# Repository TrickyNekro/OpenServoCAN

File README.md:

# OpenServoCAN
by El. Provatos

<b>!!! Currently two versions of the Hardware exist, development is going to continue on version 2 !!!</b><br>
<b>!!! Note: There is a design problem ( mechanical fitting ) with the power board, wait for update !!!</b>

An alternative to the boring control boards inside standard size hobby servos!

As it is, the project is far from completion! I have the first boards already, but I do not
have the materials to populate them. I will most probably start a gofundme campaign for these
first stages of the project. So bear with me, this will be an on-going process!

It was a very long time I wanted to make a project like this
Most, for the more expensive ones, hobby servos offer no feed back.
You send them a signal and hope they will reach the targeted position.
This might be good enough for uses in the RC world, but not good enough 
at all for those building robots or anything of a kind that needs feedback.

And thus this project was born! Although I am aware that another OpenServo Project
exists, I wanted to put my own touch into the matter and I tried to do quite a few 
things better, at least compared to the first version (I have not reviewed the second).

- Hardware V1 Capabilities

1) Added CAN-Bus! Yes, that´s a good thing! It might complicate some things especially for beginners
but that´s on what most "unobtainium" servos work in the market. I have not yet decided the 
communications protocol, but I am leaning towards CANopen, suggestions are open!

2) Can support either a potentiometer or an encoder (quadrature or not) for positional control

3) Can operate from 5V - 15V safe zone, but most probably will not have a problem with a 4S LiPo.
Current limiting will be done by software so, if you want to break the DC motor inside or not is
totally up to you!

4) Beefed up MOSFETs with individual MOSFET drivers, just to be able to push that switching 
frequency to the right spot without worrying too much!

- Hardware V2 Capabilities ( added on top of the previous! )

1) Modular! Yes, Modular! There is a Power Board, a CPU / MCU board and a Sensor / Encoder Board.
All are connected on the same bus, through some nice 0,5mm pitch - 30 pin Amphenol connectors. 
That also means of course that everything can change, and the version in connected to the function
specific board and not the whole system. Bored of the microcontroller? Change the MCU board, need
higher voltage? Change the power board? Need more capabilities? If physically allowed, add more
boards! Etc. etc. etc.. 

2) This version uses a magnetic encoder from AMS! Have not tested it yet, but given that it works
well without much interference from the motor, it should be able to give both precision, speed and
universality to the adaptation of the design. And do not forget... bored of the encoder board? Need
something more simple? Design and change it with a potentiometer board! Easy Peasy!!! 

3) One of the main limitation of the previous version was the input voltage. 15V max? How boring! 
This version was aimed to work with 24V and pushing it to 30V should be no problem! Unfortunately
the 100% duty cycle capability is gone as well, but the more efficient all N-Channel MOSFET bridge
should be able to make up the difference! Even if it does not, this was the one big step in being
able to bridge the design to a higher operating voltage, given the much constrained space.

4) There is a digital power meter from Texas Instruments on-board, should offload the processor 
quite a bit! And has also some quite interesting interrupt capabilites that should come in handy.

5) MCU board now has, EEPROM, battery (or better Super-Cap) backed RTC, a temperature sensor and
an RGB LED! How can one live without RGB these days. In all seriousness though, the RTC and EEPROM
should be a good compination for logging data / events and or even be used to wake the device up,
or even be able to develop small scripts for the device to run autonomously. But that´s only a dream
for now, still capability is there!

6) Reverse polarity protection is still here! But I also added some small extras! Some "TVS - like"
suppressors here, some more distributed capacitance there. It should be less noisy and more stable.
Only time will tell as more and more code and testing is being done!

<b> Important 2/11/2020 Update! </b>
I have officially ended the fundraiser for this Project. True to my promise I would like to thank:
Juri Ludwig, Anonymous (from eevblog ;-) ), Vagelis Logaras and Andreas Efthymiadis for their contributions.
Their money have funded a couple mouser orders, the PCBs and some test servos. Which for me is more than
enough that anyone would do for an open project with an open completion date! I can only promise that I
will continue to deliver as much as real life allows me. Thank you! Let your names be immortalized here!

# Donations!

<b>No need :) </b>

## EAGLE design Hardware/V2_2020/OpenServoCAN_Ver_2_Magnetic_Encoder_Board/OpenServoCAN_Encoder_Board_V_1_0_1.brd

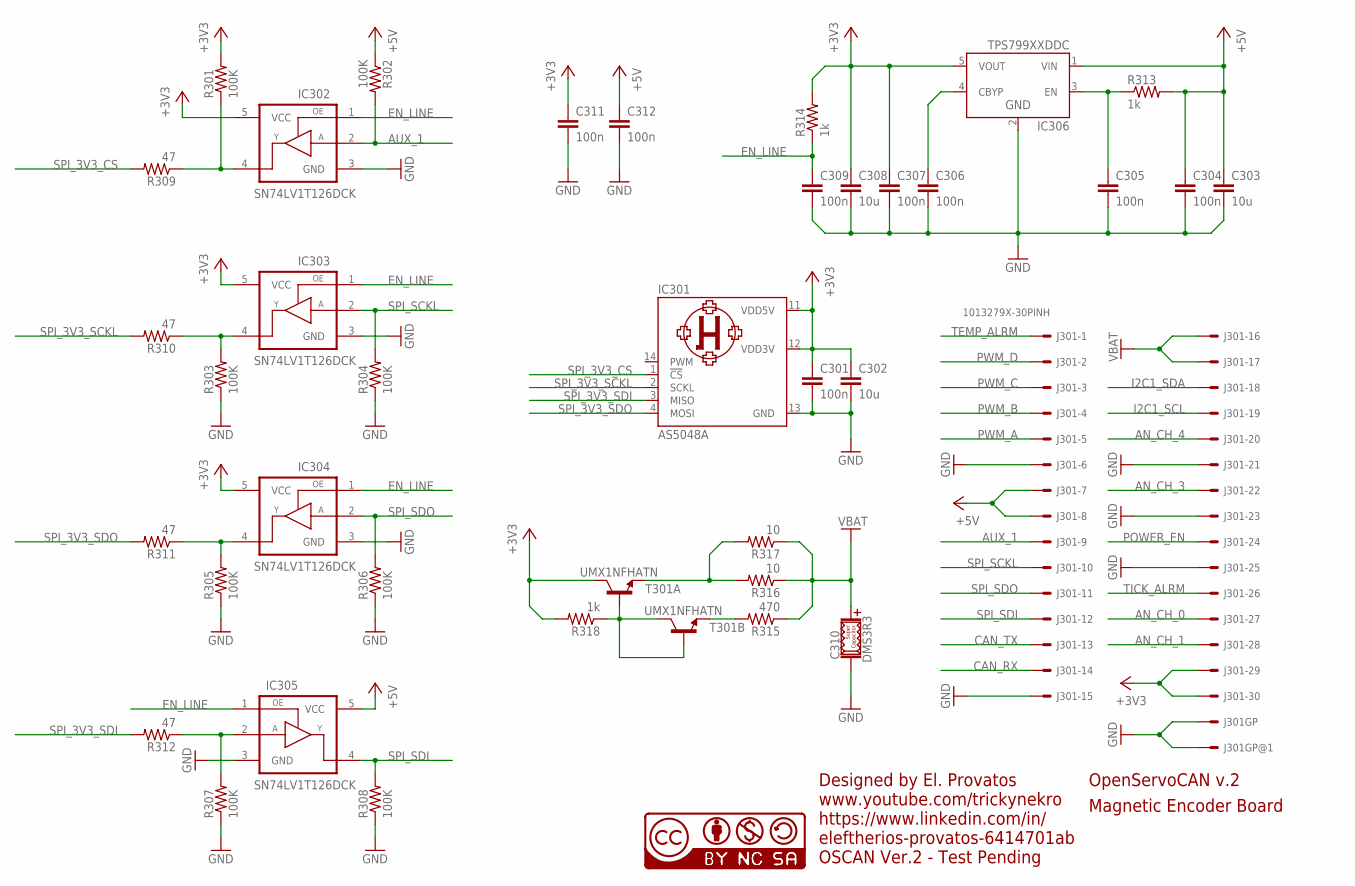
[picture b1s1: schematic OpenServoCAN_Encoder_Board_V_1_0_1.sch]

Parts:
C301, C304, C305, C306, C307, C309, C311, C312: 100n; 0402_C
C302, C303, C308: 10u; 0402_C
C310: DMS3R3; DMS_3R3_S_CAP
IC301: AS5048A; TSSOP-14
IC302, IC303, IC304, IC305: SN74LV1T126DCK; SC-70-5
IC306: TPS799XXDDC; SOT-23-5
J301: 1013279X-30PINH; 10132797-30
R301, R302, R303, R304, R305, R306, R307, R308: 100K; 0402_R
R309, R310, R311, R312: 47; 0402_R
R313, R314, R318: 1k; 0402_R
R315: 470; 0402_R
R316, R317: 10; 0402_R
T301: UMX1NFHATN; SC-70-6
U$1: CC-NC-BCNIX; CC-NC-B_NIX

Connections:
+3V3: C301.1, C302.1, C307.1, C308.1, C311.1, IC301.11 (VDD5V), IC301.12 (VDD3V), IC302.5 (VCC), IC303.5 (VCC), IC304.5 (VCC), IC306.5 (VOUT), J301.29, J301.30, R301.2, R314.2, R318.2, T301.6 (C)
+5V: C303.1, C304.1, C312.1, IC305.5 (VCC), IC306.1 (VIN), J301.7, J301.8, R302.1, R313.2
AN_CH_0: J301.27
AN_CH_1: J301.28
AN_CH_3: J301.22
AN_CH_4: J301.20
AUX_1: IC302.2 (A), J301.9, R302.2
CAN_RX: J301.14
CAN_TX: J301.13
EN_LINE: C309.1, IC302.1 (OE), IC303.1 (OE), IC304.1 (OE), IC305.1 (OE), R314.1
GND: C301.2, C302.2, C303.2, C304.2, C305.2, C306.2, C307.2, C308.2, C309.2, C310.NEG- (NEG), C311.2, C312.2, IC301.13 (GND), IC302.3 (GND), IC303.3 (GND), IC304.3 (GND), IC305.3 (GND), IC306.2 (GND), J301.6, J301.15, J301.21, J301.23, J301.25, J301.EP@2, J301.EP@↑1, R303.1, R304.1, R305.1, R306.1, R307.1, R308.1
I2C1_SCL: J301.19
I2C1_SDA: J301.18
unnamed: R318.1, T301.2 (B), T301.3 (C), T301.5 (B)
unnamed: C306.1, IC306.4 (CBYP)
unnamed: R316.2, R317.2, T301.1 (E)
unnamed: IC305.2 (A), R307.2, R312.1
unnamed: C305.1, IC306.3 (EN), R313.1
unnamed: IC304.4 (Y), R305.2, R311.1
unnamed: R315.2, T301.4 (E)
unnamed: IC303.4 (Y), R303.2, R310.1
unnamed: IC302.4 (Y), R301.1, R309.1
POWER_EN: J301.24
PWM_A: J301.5
PWM_B: J301.4
PWM_C: J301.3
PWM_D: J301.2
SPI_3V3_CS: IC301.1 (!CS), R309.2
SPI_3V3_SCKL: IC301.2 (SCKL), R310.2
SPI_3V3_SDI: IC301.3 (MISO), R312.2
SPI_3V3_SDO: IC301.4 (MOSI), R311.2
SPI_SCKL: IC303.2 (A), J301.10, R304.2
SPI_SDI: IC305.4 (Y), J301.12, R308.2
SPI_SDO: IC304.2 (A), J301.11, R306.2
TEMP_ALRM: J301.1
TICK_ALRM: J301.26
VBAT: C310.POS+ (POS), J301.16, J301.17, R315.1, R316.1, R317.1

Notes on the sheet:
OpenServoCAN v.2
Magnetic Encoder Board
Designed by El. Provatos
www.youtube.com/trickynekro
https://www.linkedin.com/in/ eleftherios-provatos-6414701ab
OSCAN Ver.2 - Test Pending

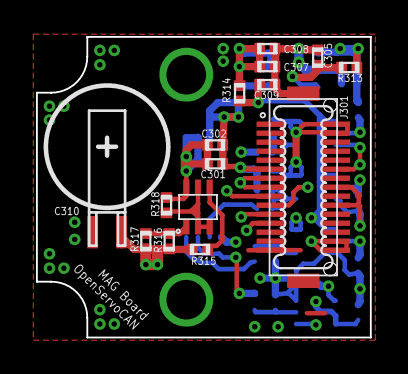
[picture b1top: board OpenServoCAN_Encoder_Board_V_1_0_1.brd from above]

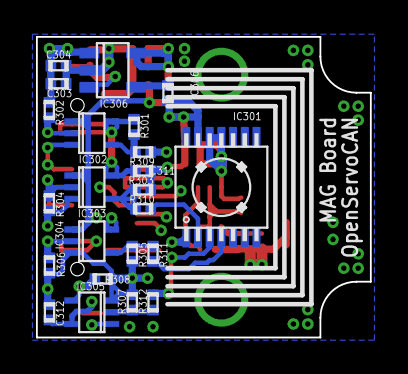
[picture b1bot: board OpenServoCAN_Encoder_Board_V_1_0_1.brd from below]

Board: 4 copper layers, 18.6 x 16.7 mm, 39 parts (23 on the bottom side), 22 nets.

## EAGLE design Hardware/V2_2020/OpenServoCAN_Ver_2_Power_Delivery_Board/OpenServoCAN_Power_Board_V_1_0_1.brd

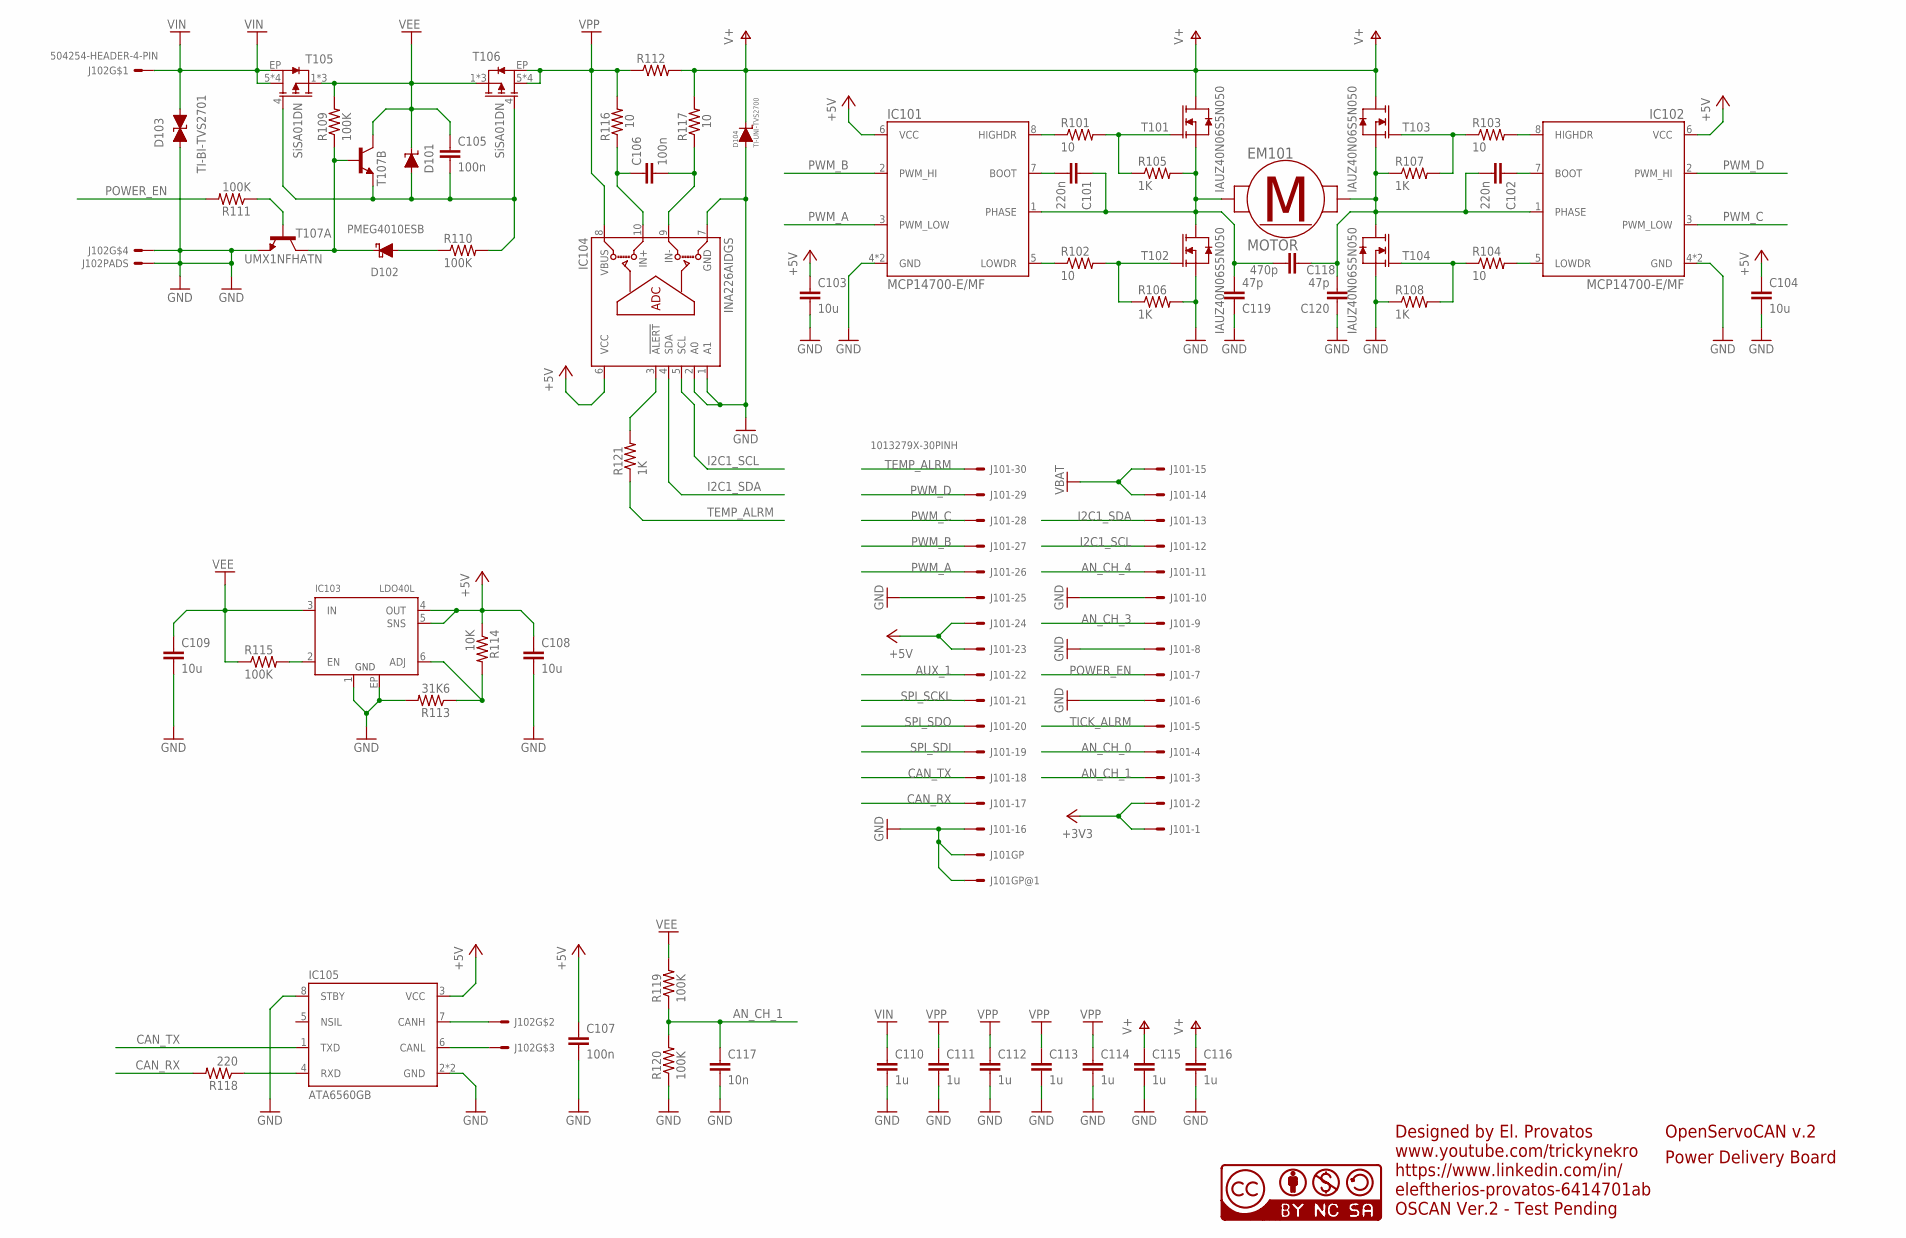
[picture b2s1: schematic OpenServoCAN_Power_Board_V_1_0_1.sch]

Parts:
C101, C102: 220n; 0603_C
C103, C104, C108, C109: 10u; 0402_C
C105, C106, C107: 100n; 0402_C
C110, C111, C112, C113, C114, C115, C116: 1u; 0603_C
C117: 10n; 0402_C
C118: 470p; 1206_C
C119, C120: 47p; 1206_C
D101: DDZ12CSF; SOD-323
D102: PMEG4010ESB; DSN1006-2
D103: TI-BI-TVS2701; VSON-8-DRB0008A
D104: TI-UNI-TVS2700; WSON-6
EM101: MOTOR; RF-020TH-10210
IC101, IC102: MCP14700-E/MF; DFN_8_3X3X09_MF_MICROCHIP
IC103: LDO40L; DFN6-3X3
IC104: INA226AIDGS; VSSOP-10
IC105: ATA6560GB; VDFN-8-EP
J101: 1013279X-30PINH; 10132797-30
J102: 504254-HEADER-4-PIN; 504254
R101, R102, R103, R104, R116, R117: 10; 0402_R
R105, R106, R107, R108, R121: 1K; 0402_R
R109, R110, R111, R115, R119, R120: 100K; 0402_R
R112: TLR2HW-R-US-SENSE; TLR2HW
R113: 31K6; 0402_R
R114: 10K; 0402_R
R118: 220; 0402_R
T101, T102, T103, T104: IAUZ40N06S5N050; PG-TSDSON-8-33-INF
T105, T106: SiSA01DN; POWERPAK-1212-8-SINGLE
T107: UMX1NFHATN; SC-70-6
U$1: CC-NC-BCNIX; CC-NC-B_NIX

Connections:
+3V3: J101.1, J101.2
+5V: C103.1, C104.1, C107.1, C108.1, IC101.6 (VCC), IC102.6 (VCC), IC103.4 (OUT), IC103.5 (SNS), IC104.6 (VCC), IC105.3 (VCC), J101.23, J101.24, R114.1
AN_CH_0: J101.4
AN_CH_1: C117.1, J101.3, R119.1, R120.2
AN_CH_3: J101.9
AN_CH_4: J101.11
AUX_1: J101.22
CAN_RX: J101.17, R118.2
CAN_TX: IC105.1 (TXD), J101.18
GND: C103.2, C104.2, C107.2, C108.2, C109.2, C110.2, C111.2, C112.2, C113.2, C114.2, C115.2, C116.2, C117.2, C119.1, C120.1, D103.5 (A), D103.6 (A), D103.7 (A), D103.8 (A), D104.1 (A), D104.2 (A), D104.3 (A), D104.EP (A), IC101.4 (GND), IC101.EP (GND), IC102.4 (GND), IC102.EP (GND), IC103.1 (GND), IC103.EP (GND), IC104.1 (A1), IC104.2 (A0), IC104.7 (GND), IC105.2 (GND), IC105.8 (STBY), IC105.EP (GND), J101.6, J101.8, J101.10, J101.16, J101.25, J101.EP@2, J101.EP@↑1, J102.4, J102.EP@1, J102.EP@2, J102.EP@3, J102.EP@4, R106.2, R108.1, R113.2, R120.1, T102.S, T104.S, T107.1 (E)
I2C1_SCL: IC104.5 (SCL), J101.12
I2C1_SDA: IC104.4 (SDA), J101.13
unnamed: C101.1, C118.2, C119.2, EM101.1B (1), EM101.1T (1), IC101.1 (PHASE), R105.2, T101.S, T102.D
unnamed: C102.2, C118.1, C120.2, EM101.2B (2), EM101.2T (2), IC102.1 (PHASE), R107.1, T103.S, T104.D
unnamed: R103.1, R107.2, T103.G
unnamed: IC101.8 (HIGHDR), R101.1
unnamed: R101.2, R105.1, T101.G
unnamed: IC102.8 (HIGHDR), R103.2
unnamed: IC104.3 (!ALERT), R121.2
unnamed: R102.2, R106.1, T102.G
unnamed: IC101.5 (LOWDR), R102.1
unnamed: R104.1, R108.2, T104.G
unnamed: IC102.5 (LOWDR), R104.2
unnamed: C102.1, IC102.7 (BOOT)
unnamed: IC103.6 (ADJ), R113.1, R114.2
unnamed: C101.2, IC101.7 (BOOT)
unnamed: IC103.2 (EN), R115.2
unnamed: C106.1, IC104.10 (IN+), R116.1
unnamed: C106.2, IC104.9 (IN-), R117.1
unnamed: IC105.7 (CANH), J102.2
unnamed: IC105.6 (CANL), J102.3
unnamed: D102.K, R109.1, T107.5 (B), T107.6 (C)
unnamed: D102.A, R110.1
unnamed: C105.2, D101.A, R110.2, T105.4 (G), T106.4 (G), T107.4 (E)
unnamed: R111.1, T107.2 (B)
unnamed: IC105.4 (RXD), R118.1
POWER_EN: J101.7, R111.2
PWM_A: IC101.3 (PWM_LOW), J101.26
PWM_B: IC101.2 (PWM_HI), J101.27
PWM_C: IC102.3 (PWM_LOW), J101.28
PWM_D: IC102.2 (PWM_HI), J101.29
SPI_SCKL: J101.21
SPI_SDI: J101.19
SPI_SDO: J101.20
TEMP_ALRM: J101.30, R121.1
TICK_ALRM: J101.5
V+: C115.1, C116.1, D104.4 (K), D104.5 (K), D104.6 (K), R112.2, R117.2, T101.D, T103.D
VBAT: J101.14, J101.15
VEE: C105.1, C109.1, D101.K, IC103.3 (IN), R109.2, R115.1, R119.2, T105.1 (S), T105.2 (S), T105.3 (S), T106.1 (S), T106.2 (S), T106.3 (S), T107.3 (C)
VIN: C110.1, D103.1 (K), D103.2 (K), D103.3 (K), D103.4 (K), J102.1, T105.5 (D), T105.6 (D), T105.7 (D), T105.8 (D), T105.EP (D)
VPP: C111.1, C112.1, C113.1, C114.1, IC104.8 (VBUS), R112.1, R116.2, T106.5 (D), T106.6 (D), T106.7 (D), T106.8 (D), T106.EP (D)

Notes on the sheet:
Designed by El. Provatos
www.youtube.com/trickynekro
https://www.linkedin.com/in/ eleftherios-provatos-6414701ab
OSCAN Ver.2 - Test Pending
OpenServoCAN v.2
Power Delivery Board

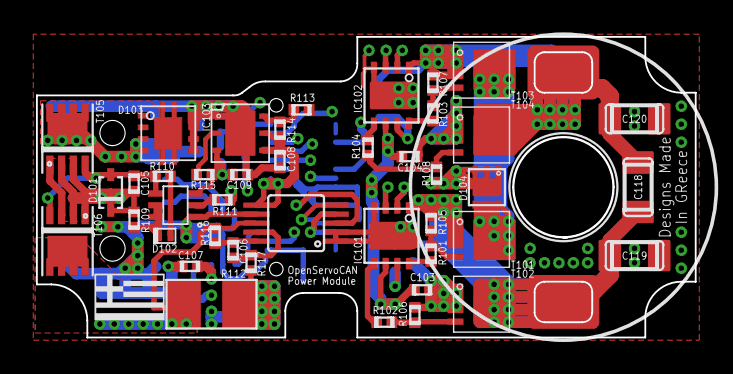
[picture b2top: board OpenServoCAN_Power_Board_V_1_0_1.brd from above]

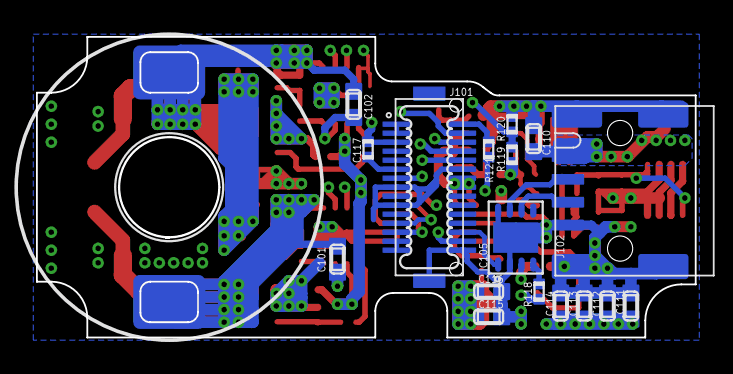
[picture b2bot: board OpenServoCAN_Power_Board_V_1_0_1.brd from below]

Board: 4 copper layers, 36.6 x 16.7 mm, 61 parts (18 on the bottom side), 43 nets.

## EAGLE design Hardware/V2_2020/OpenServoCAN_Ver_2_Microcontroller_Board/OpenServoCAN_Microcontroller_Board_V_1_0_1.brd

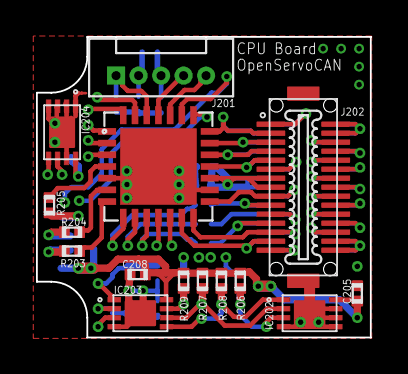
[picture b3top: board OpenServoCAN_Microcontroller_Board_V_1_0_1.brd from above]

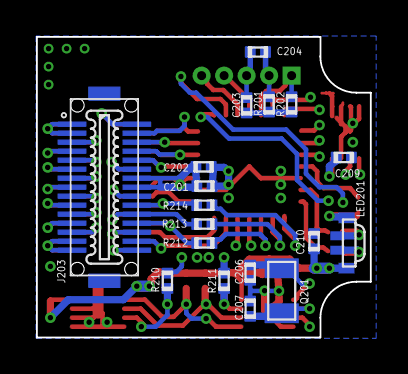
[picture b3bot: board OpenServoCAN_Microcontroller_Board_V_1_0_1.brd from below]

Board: 4 copper layers, 18.6 x 16.7 mm, 35 parts (18 on the bottom side), 40 nets.

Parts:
C201, C203, C204, C205, C208, C209, C210: 100n; 0402_C
C202: 2u2; 0402_C
C206, C207: 22p; 0402_C
IC201: QFN-28
IC202: MCP9808T-E/MC; DFN_2X3_MICROCHIP
IC203: MCP7940N; DFN_2X3_MICROCHIP
IC204: 24XX64MC; DFN_2X3_MICROCHIP
J201: PICOBLADE-5
J202, J203: 1013279X-30PINR; 10132798-30
LED201: 1206_RGB_LED
LOGO1: TRN_LOGO_INV; TRN_LOGO_2020_INV
Q201: LFXTAL009678
R201, R206, R207, R208, R209: 4k7; 0402_R
R202, R210, R211: 470; 0402_R
R203, R204, R205: 220; 0402_R
R212, R213, R214: 47; 0402_R
U$1: CC-NC-BCNIX; CC-NC-B_NIX

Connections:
+3V3: J202.29, J202.30, J203.1, J203.2
+5V: C201.1, C202.1, C204.1, C205.1, C208.1, C209.1, C210.1, IC201.17, IC202.8, IC203.8, IC204.8, J201.2, J202.7, J202.8, J203.23, J203.24, LED201.3, R201.2, R206.2, R207.2, R208.2, R209.2
AN_CH_0: IC201.27, J202.27, J203.4
AN_CH_1: IC201.28, J202.28, J203.3
AN_CH_3: IC201.2, J202.22, J203.9
AN_CH_4: IC201.3, J202.20, J203.11
AUX_1: IC201.15, J202.9, J203.22
CAN_RX: IC201.13, J202.14, J203.17
CAN_TX: IC201.14, J202.13, J203.18
GND: C201.2, C202.2, C203.2, C204.2, C205.2, C206.2, C207.2, C208.2, C209.2, C210.2, IC201.5, IC201.16, IC201.EP, IC202.4, IC202.5, IC202.6, IC202.7, IC202.EP, IC203.4, IC203.EP, IC204.1, IC204.2, IC204.3, IC204.4, IC204.7, IC204.EP, J201.3, J202.6, J202.15, J202.21, J202.23, J202.25, J202.EP@2, J202.EP@↑1, J203.6, J203.8, J203.10, J203.16, J203.25, J203.EP@2, J203.EP@↑1
I2C1_SCL: IC201.11, IC202.2, IC203.6, IC204.6, J202.19, J203.12, R207.1
I2C1_SDA: IC201.12, IC202.1, IC203.5, IC204.5, J202.18, J203.13, R208.1
LED_B: IC201.7, R203.2
LED_G: IC201.6, R204.2
LED_R: IC201.4, R205.2
unnamed: C203.1, R201.1, R202.2
unnamed: IC201.26, J201.1, R202.1
unnamed: IC201.24, J201.5
unnamed: IC202.3, R206.1, R210.1
unnamed: IC201.25, J201.4
unnamed: LED201.2, R204.1
unnamed: LED201.4, R205.1
unnamed: LED201.1, R203.1
unnamed: IC203.7, R209.1, R211.1
unnamed: C206.1, IC203.1, Q201.P$2
unnamed: C207.1, IC203.2, Q201.P$1
unnamed: IC201.10, R212.1
unnamed: IC201.9, R213.2
unnamed: IC201.8, R214.2
POWER_EN: IC201.1, J202.24, J203.7
PWM_A: IC201.18, J202.5, J203.26
PWM_B: IC201.19, J202.4, J203.27
PWM_C: IC201.20, J202.3, J203.28
PWM_D: IC201.21, J202.2, J203.29
SPI_SCKL: J202.10, J203.21, R214.1
SPI_SDI: J202.12, J203.19, R212.2
SPI_SDO: J202.11, J203.20, R213.1
TEMP_ALRM: IC201.23, J202.1, J203.30, R210.2
TICK_ALRM: IC201.22, J202.26, J203.5, R211.2
VBAT: IC203.3, J202.16, J202.17, J203.14, J203.15

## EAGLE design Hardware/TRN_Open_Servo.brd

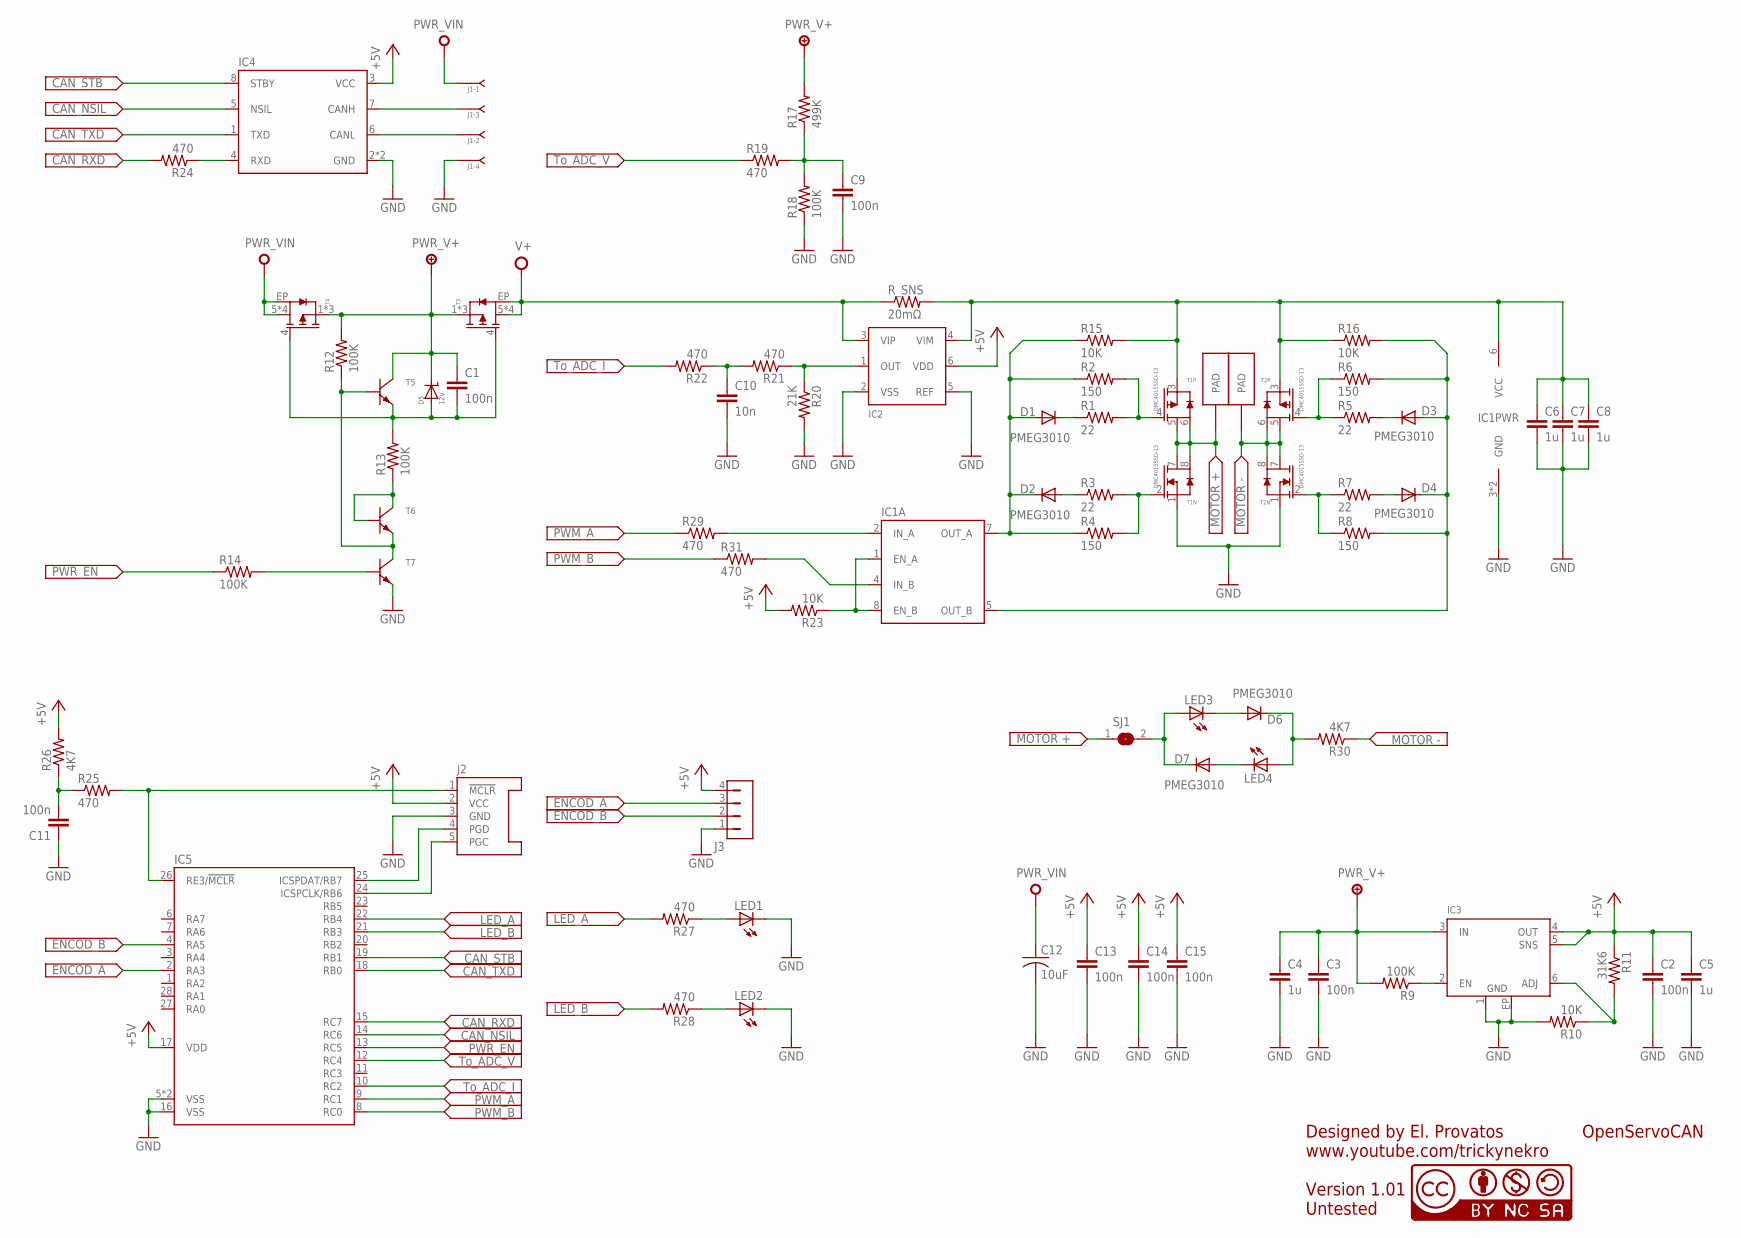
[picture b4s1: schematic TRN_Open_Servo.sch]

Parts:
C1, C2, C3, C9, C11, C13, C14, C15: 100n; C0402
C4, C5, C6, C7, C8: 1u; C0603K
C10: 10n; C0402
C12: 10uF; C1210
D1, D2, D3, D4, D6, D7: PMEG3010; SOD523
D5: 12V; SOD-323
IC1: MCP14A0454MNY; TDFN-8-EP
IC2: MCP6C02SMD; SOT-23-6
IC3: LDO40L-ADJ; DFN6-3X3
IC4: ATA6560GB; VDFN-8-EP
IC5: PIC18F26K83ML; QFN-28
J1: J-04-SIP-100; SIP-100-04
J2: PIC-ICSP-MICRO; PICOBLADE-5
J3: 1X4_PICOBLADE_CONNECTOR; PICOBLADE-4
LED1, LED2, LED3, LED4: LEDCHIP-LED0603; CHIP-LED0603
PAD1, PAD2: PLATED_SLOT
R1, R3, R5, R7: 22; R0402
R2, R4, R6, R8: 150; R0402
R9, R12, R13, R14, R18: 100K; R0402
R10, R15, R16, R23: 10K; R0402
R11: 31K6; R0402
R17: 499K; R0402
R19, R21, R22, R24, R25, R27, R28, R29, R31: 470; R0402
R20: 21K; R0402
R26, R30: 4K7; R0402
R_SNS: 20mΩ; R0805
SJ1: SJ
T1, T2: DMC4015SSD-13; SO-8
T3, T4: SISA01DN; POWERPAK-1212-8
T5, T6, T7: MMBT2222AM3T5G; SOT-723-3
U$1: CC-NC-BCNIX; CC-NC-B_NIX

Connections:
+5V: C2.1, C5.1, C13.1, C14.1, C15.1, IC2.6 (VDD), IC3.4 (OUT), IC3.5 (SNS), IC4.3 (VCC), IC5.17 (VDD), J2.2 (VCC), J3.4, R11.1, R23.2, R26.2
CAN_NSIL: IC4.5 (NSIL), IC5.14 (RC6)
CAN_RXD: IC5.15 (RC7), R24.2
CAN_STB: IC4.8 (STBY), IC5.19 (RB1)
CAN_TXD: IC4.1 (TXD), IC5.18 (RB0)
ENCOD_A: IC5.2 (RA3), J3.3
ENCOD_B: IC5.4 (RA5), J3.2
GND: C2.2, C3.2, C4.2, C5.2, C6.2, C7.2, C8.2, C9.2, C10.2, C11.1, C12.2, C13.2, C14.2, C15.2, IC1.3 (GND), IC1.EP (GND), IC2.2 (VSS), IC2.5 (REF), IC3.1 (GND), IC3.EP (GND), IC4.2 (GND), IC4.EP (GND), IC5.5 (VSS), IC5.16 (VSS), IC5.EP (VSS), J1.4, J2.3 (GND), J3.1, LED1.C, LED2.C, R10.2, R18.1, R20.2, T1.1 (S), T2.1 (S), T7.2 (E)
LED_A: IC5.22 (RB4), R27.2
LED_B: IC5.21 (RB3), R28.2
MOTOR+: PAD1.P$1, PAD1.P$2, SJ1.1, T1.5 (D), T1.6 (D), T1.7 (D), T1.8 (D)
MOTOR-: PAD2.P$1, PAD2.P$2, R30.1, T2.5 (D), T2.6 (D), T2.7 (D), T2.8 (D)
unnamed: D7.C, LED3.A, SJ1.2
unnamed: IC3.2 (EN), R9.1
unnamed: D6.C, LED4.A, R30.2
unnamed: D3.A, D4.C, IC1.5 (OUT_B), R6.2, R8.2, R16.2
unnamed: D1.A, D2.C, IC1.7 (OUT_A), R2.1, R4.1, R15.1
unnamed: D1.C, R1.1
unnamed: R1.2, R2.2, T1.4 (G)
unnamed: R3.2, R4.2, T1.2 (G)
unnamed: D2.A, R3.1
unnamed: D3.C, R5.2
unnamed: R5.1, R6.1, T2.4 (G)
unnamed: R7.1, R8.1, T2.2 (G)
unnamed: D4.A, R7.2
unnamed: IC3.6 (ADJ), R10.1, R11.2
unnamed: C6.1, C7.1, C8.1, IC1.6 (VCC), IC2.4 (VIM), R15.2, R16.1, R_SNS.2, T1.3 (S), T2.3 (S)
unnamed: R12.1, T5.1 (B), T6.2 (E), T7.3 (C)
unnamed: IC4.7 (CANH), J1.3
unnamed: C1.2, D5.A, R13.2, T3.4 (G), T4.4 (G), T5.2 (E)
unnamed: R13.1, T6.1 (B), T6.3 (C)
unnamed: IC4.6 (CANL), J1.2
unnamed: C9.1, R17.1, R18.2, R19.2
unnamed: IC1.1 (EN_A), IC1.8 (EN_B), R23.1
unnamed: R14.2, T7.1 (B)
unnamed: IC5.26 (RE3/!MCLR!), J2.1 (!MCLR), R25.2
unnamed: C11.2, R25.1, R26.1
unnamed: LED1.A, R27.1
unnamed: IC2.1 (OUT), R20.1, R21.1
unnamed: IC5.24 (ICSPCLK/RB6), J2.5 (PGC)
unnamed: IC5.25 (ICSPDAT/RB7), J2.4 (PGD)
unnamed: C10.1, R21.2, R22.1
unnamed: IC4.4 (RXD), R24.1
unnamed: D6.A, LED3.C
unnamed: D7.A, LED4.C
unnamed: LED2.A, R28.1
unnamed: IC1.2 (IN_A), R29.2
unnamed: IC1.4 (IN_B), R31.2
PWM_A: IC5.9 (RC1), R29.1
PWM_B: IC5.8 (RC0), R31.1
PWR_EN: IC5.13 (RC5), R14.1
PWR_V+: C1.1, C3.1, C4.1, D5.K, IC3.3 (IN), R9.2, R12.2, R17.2, T3.1 (S), T3.2 (S), T3.3 (S), T4.1 (S), T4.2 (S), T4.3 (S), T5.3 (C)
PWR_VIN: C12.1, J1.1, T4.5 (D), T4.6 (D), T4.7 (D), T4.8 (D), T4.EP (D)
TO_ADC_I: IC5.10 (RC2), R22.2
TO_ADC_V: IC5.12 (RC4), R19.1
V+: IC2.3 (VIP), R_SNS.1, T3.5 (D), T3.6 (D), T3.7 (D), T3.8 (D), T3.EP (D)

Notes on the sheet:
OpenServoCAN
Designed by El. Provatos
Version 1.01
www.youtube.com/trickynekro
Untested

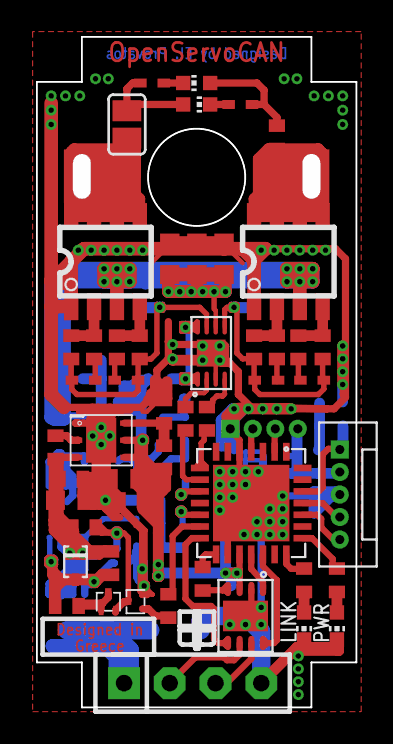
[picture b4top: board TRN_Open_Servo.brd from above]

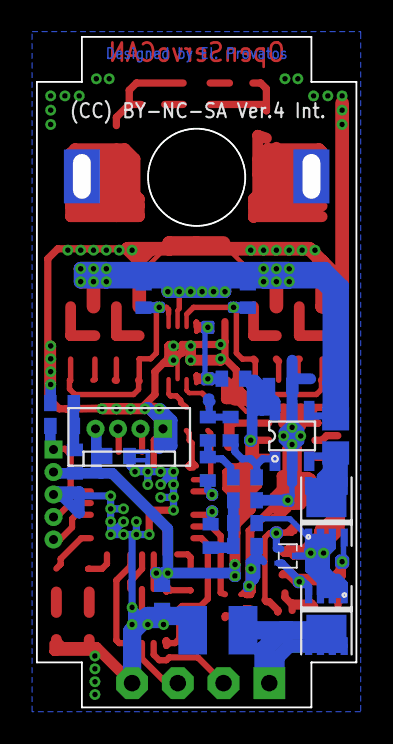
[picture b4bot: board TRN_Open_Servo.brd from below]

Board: 2 copper layers, 16.9 x 36.3 mm, 77 parts (24 on the bottom side), 56 nets.

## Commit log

2020-03-28 commit message
2020-06-15 #1 Timer_Support_Library
2020-08-03 #1 Some Suport for MCU peripherals added
    - Added support for PWM related timers and comperators.
    - Next update should handle the Interrupts
2020-08-07 #1 Added Interrupt Service Routines (Empty) - Added Initial Supprot for CWG Modules
2020-12-01 #2
    File Preparing Step 1
2021-01-04 #2 Hardware Ver.2 Upload
    All three boards of Version 2 are uploaded:
    - Power Delivery Board ver 1.01
    - Microcontroller Board ver 1.01
    - Magnetic Encoder Board ver 1.01
    I have to see if I need to utilize enable pin of the 3V3 Regulator of the magnetic board to lower power consumption on idle, but for now that is good enough!
    I also have to see if I can fit another board in there, cause then we are going for accelerometer and gyro! And that could be the end game for "edge controlling (ahem computing).
2021-06-22 Note to PCB changes
    Layout of the Power Board PCB has to be changed.
2021-07-02 PWM, Timers and PPS
    - Fixed Timer 2 / 4 / 6 libraries. Fixed logic errors in the libraries.
    - Added the Libraries for PWM 5 / 6 / 7 / 8.
    - Fixed / Configured Correctly the PPS for outputs.
    NOTE: PPS is different for inputs and outputs. A pin is configured with a module output. A module input is configured with a pin.
    Demo: RGB LED Demo cycling colors.
2026-05-02 Update LICENSE.txt
    Updated year.
2026-05-02 Update README.md
    As this project is and will remain in a long hiatus, until I can get time to finish it off, there is no need for any donation links or addresses to be present.

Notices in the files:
parts and their libraries:
con-headers-jp: Copyright (C) 2004, Bob Starr (rtzaudio@mindspring.com)
cc-by-nc-sa: All hardware is licensed under the Creative Commons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
supply0: Copyright (C) 2007, Bob Starr
